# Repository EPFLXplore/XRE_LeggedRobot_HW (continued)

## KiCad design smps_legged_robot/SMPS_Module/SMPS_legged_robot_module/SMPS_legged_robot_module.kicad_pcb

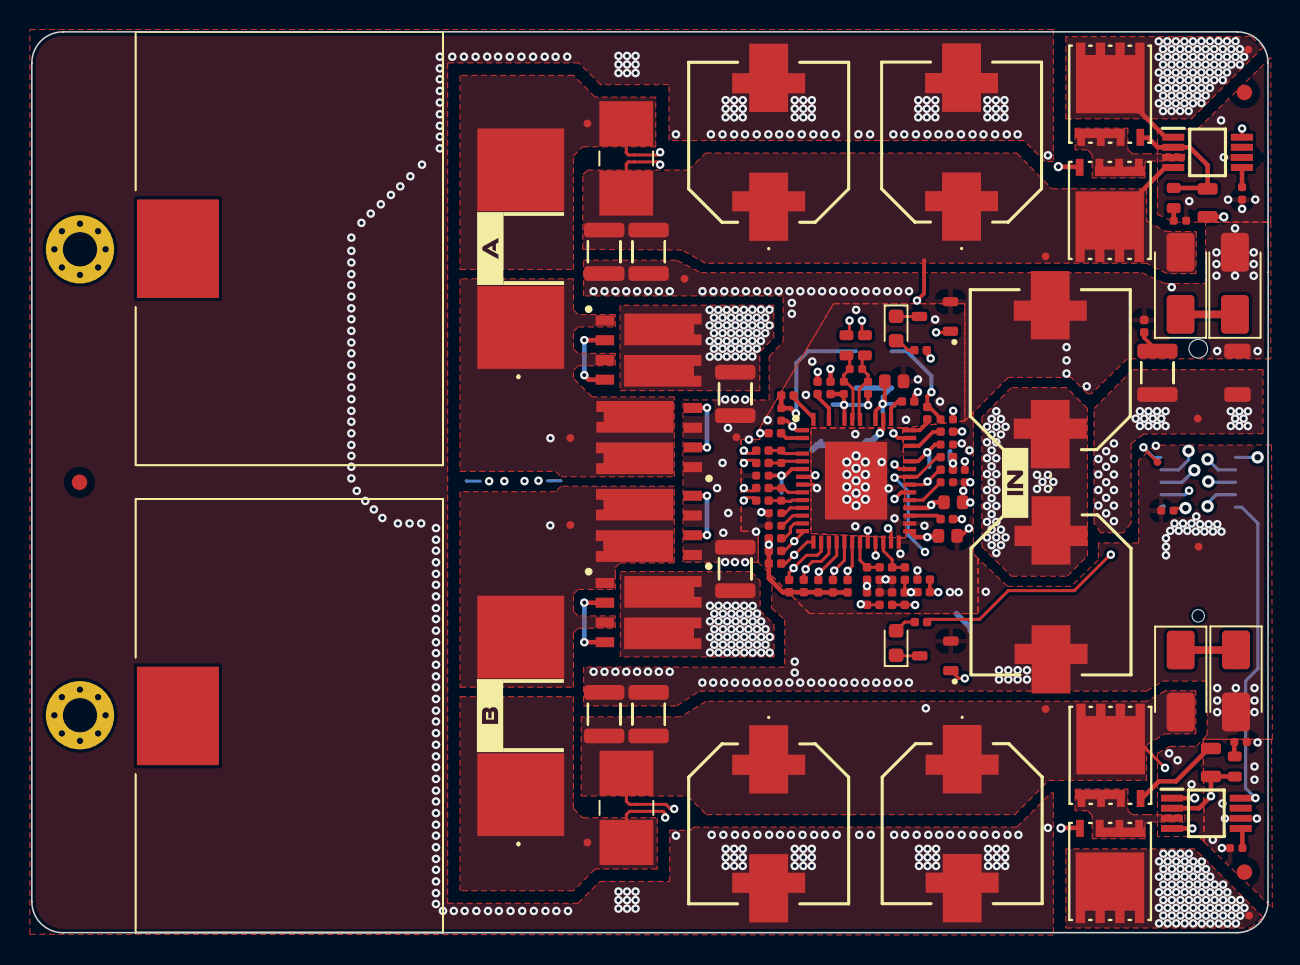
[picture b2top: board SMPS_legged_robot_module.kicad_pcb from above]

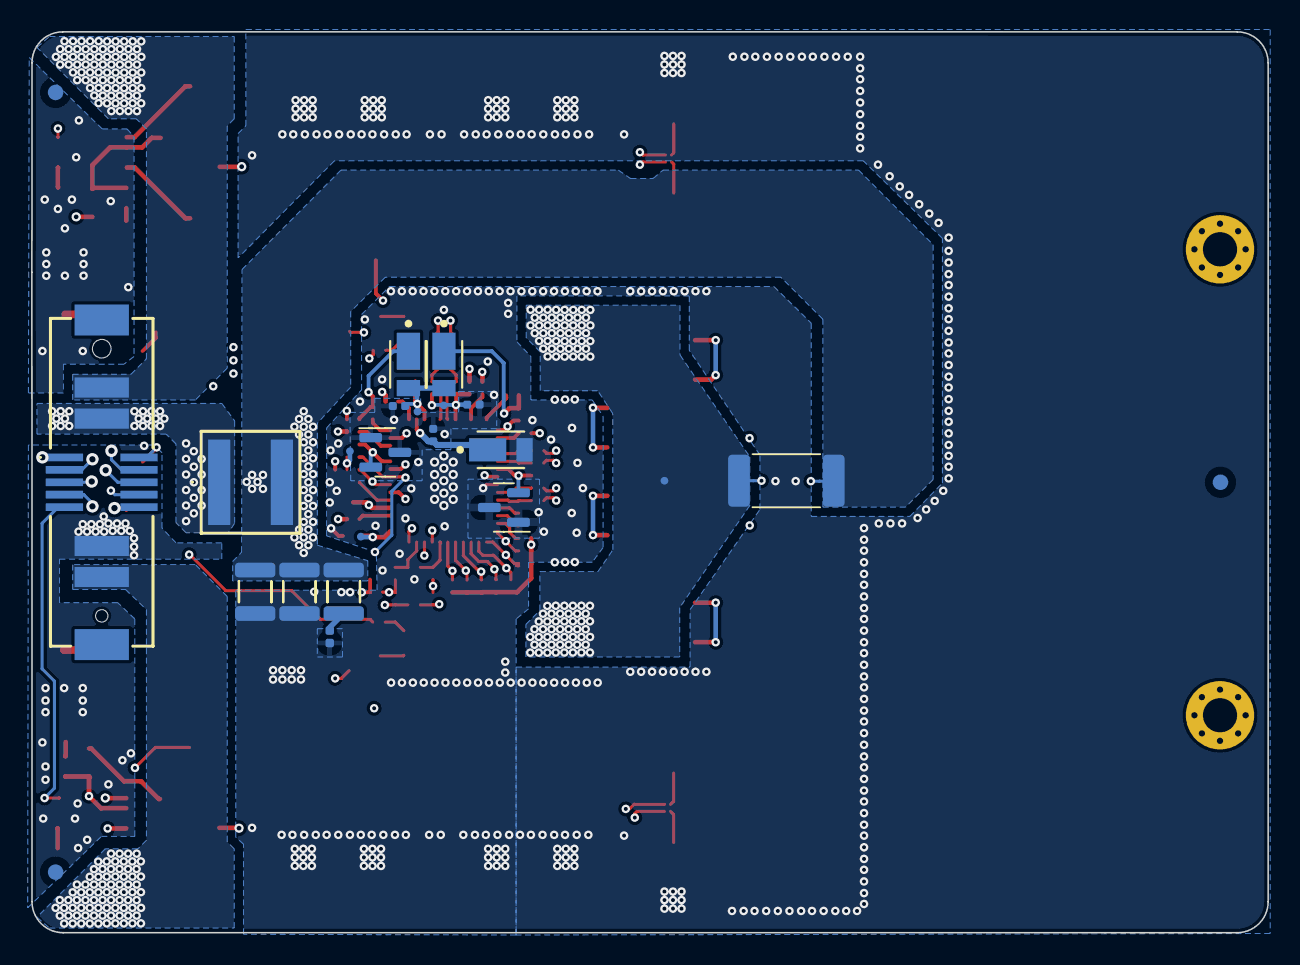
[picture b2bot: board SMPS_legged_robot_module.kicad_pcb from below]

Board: 6 copper layers, 79.6 x 58.0 mm, 156 parts (25 on the bottom side), 83 nets.

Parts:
C401, C601, C603, C702, C715: 100n X7R 50V; C_0402_1005_DensityHigh
C602, C604, C708, C713, C718, C722, C723: 10n X7R 100V; C_0402_1005_DensityHigh
C607: 1u X7R 25V; C_0603_1608_DensityHigh
C701, C706, C707, C714, C731, C732, C901, C903, C906, C907: 10uF X7R 100V; C_1210_3225_DensityHigh
C703, C720, C725: 1n X7R 100V; C_0402_1005_DensityHigh
C704, C705, C729, C730: 120u CAN 50V; Hybrid_G_VP
C709, C712: 33p X7R 25V; C_0402_1005_DensityHigh
C710, C711: 6.8n X7R 25V; C_0402_1005_DensityHigh
C716, C726: 2.2u X7R 25V; C_0603_1608_DensityHigh
C717, C724: 4.7u X5R 25V; C_0402_1005_DensityHigh
C902: 4u7 X7R 100V; C_1206_3216_DensityHigh
C904, C905: 56u CAN 63V; Hybrid_G_VP
D601, D602, D703: DFLS1100-7; Diodes_Inc.-PowerDI123-03_2017-0-MFG
D603, D605: SMAJ28A; D_SMA
D604, D606: SMAJ33A; D_SMA
D701, D702: GREEN; LED_0603_1608Metric
FM701, FM702, FM703, FM704, FM705, FM706: Fiducial; Fiducial_1mm_Mask2mm
H801, H802: M2 (2.2mm); MountingHole_2.2mm_M2_Pad_Via
IC601, IC602: LTC4372CMS8#TRPBF; SOP65P490X110-8N
IC701: LTC3889EUKG#PBF; QFN50P700X800X80-53N-D
J401: 10159559-410221RLF; 10159559410221RLF
L701, L702: 4,7uH; PQ2617BHA4R7K
L901: 1u XEL6060-102MEB; XEL6060102MEC
NT601, NT602, NT603, NT604, NT605, NT606: NetTie_2; NetTie-2_SMD_Pad0.2mm
Q601, Q602, Q603, Q604: BSC016N06NSATMA1; PG-TDSON-8_INF
Q701, Q702, Q705, Q706: IPG20N06S4L26AATMA1; Infineon-IPG20N06S4L-26A-Manufacturer_Recommended
Q703, Q704: PMBT3906,215; SOT-23
Q707, Q708: NX3020NAK,215; SOT-23-3
R601, R603: 10R 1% 1/8W; R_0805_2012_DensityHigh
R602, R604, R727, R728: 1k 1% 1/10W; R_0603_1608_DensityHigh
R701: 5k 1% 1/16W; R_0402_1005_DensityHigh
R702, R703, R704, R705, R706, R707, R708, R709, R710, R711: 10k 1% 1/16W; R_0402_1005_DensityHigh
R712, R713, R714, R715, R716, R718, R719, R720, R721, R722: R; R_0402_1005_DensityHigh
R717, R729: 3m 1% 3W; RESC6432X135N
R723, R724, R730, R731, R901, R902: 10R 1% 1/8W; R_0402_1005_DensityHigh
R725: 2m 1% 3W; R_2512_6332Metric_Pad1.40x3.35mm_HandSolder
R726, R732, R733, R734, R735, R738, R739: 2R 1% 1/8W; R_0402_1005_DensityHigh
R736, R737: 470R 1% 1/8W; R_0402_1005_DensityHigh
TP401: FAULT0; TestPoint_Pad_D0.5mm_Front
TP402: FAULT1; TestPoint_Pad_D0.5mm_Front
TP403: SDA; TestPoint_Pad_D0.5mm_Front
TP404: SCL; TestPoint_Pad_D0.5mm_Front
TP405: RUN0; TestPoint_Pad_D0.5mm_Front
TP406: RUN1; TestPoint_Pad_D0.5mm_Front
TP407: ALERT; TestPoint_Pad_D0.5mm_Front
TP408: +VBAT_IN; TestPoint_Pad_D0.5mm_Front
TP409: +12V; TestPoint_Pad_D0.5mm_Front
TP410, TP413, TP414: GND; TestPoint_Pad_D0.5mm_Front
TP411: MVA; TestPoint_Pad_D0.5mm_Front
TP412: MVB; TestPoint_Pad_D0.5mm_Front
TP701: VIN; TestPoint_Pad_D0.5mm_Front
TP702: SW0; TestPoint_Pad_D0.5mm_Front
TP703: SW1; TestPoint_Pad_D0.5mm_Front
TP704: 2V5LTC; TestPoint_Pad_D0.5mm_Back
TP705: 3V3LTC; TestPoint_Pad_D0.5mm_Back
TP706: DRVCC; TestPoint_Pad_D0.5mm_Back
TP707: MVB_OUT; TestPoint_Pad_D0.5mm_Front
TP708: MVA_OUT; TestPoint_Pad_D0.5mm_Front
TP709: VIN_MOS; TestPoint_Pad_D0.5mm_Front
TP710: SW0_L; TestPoint_Pad_D0.5mm_Front
TP711: SW1_L; TestPoint_Pad_D0.5mm_Front
kibuzzard-66485E02: G***; kibuzzard-66485E02
kibuzzard-66485E57: G***; kibuzzard-66485E57
kibuzzard-66485E80: G***; kibuzzard-66485E80

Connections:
+2V5LTC: C726.2, IC701.27 (VDD25), R712.1, R713.1, R714.1, R715.1, R716.1, TP704.1
+3.3VLTC: C716.2, IC701.30 (VDD33), R701.2, R702.2, R703.2, R704.2, R705.2, R706.2, R707.2, R708.2, R709.2, R710.2, R711.2, TP705.1
+12V: C401.1, C717.2, D703.1 (K), IC701.43 (EXTVCC), J401.S10, R736.1, R737.1, TP409.1
/Project Architecture/+VBAT_Filtered: C903.1, C904.1, C905.1, C906.1, C907.1, L901.2, NT602.1, R725.1, R726.2
/Project Architecture/+VBAT_IN: C901.1, C902.1, J401.P1, L901.1, TP408.1
/Project Architecture/MVA_FILTERED: IC601.1 (OUT), J401.P3, Q602.1 (D), TP411.1
/Project Architecture/MVB_FILTERED: IC602.1 (OUT), J401.P4, Q604.1 (D), TP412.1
/Project Architecture/Power - Connector /MVA_SHDN: IC601.8 (SHDN), J401.S8
/Project Architecture/Power - Connector /MVB_SHDN: IC602.8 (SHDN), J401.S9
/Project Architecture/Power - Connector /RUN0: IC701.19 (RUN0), J401.S4, R705.1, TP405.1
/Project Architecture/Power - Connector /RUN1: IC701.20 (RUN1), J401.S2, R704.1, TP406.1
/Project Architecture/Power - Connector /SCL: IC701.14 (SCL), J401.S1, R710.1, TP404.1
/Project Architecture/Power - Connector /SDA: IC701.15 (SDA), J401.S3, R711.1, TP403.1
/Project Architecture/Power - Connector /~ALERT: IC701.16 (~ALERT), J401.S5, R709.1, TP407.1
/Project Architecture/Power - Connector /~FAULT0: IC701.17 (~FAULT0), J401.S7, R708.1, TP401.1
/Project Architecture/Power - Connector /~FAULT1: IC701.18 (~FAULT1), J401.S6, R707.1, TP402.1
/Project Architecture/Power - Converter/DRVCC: C607.2, C724.2, D601.2 (A), D602.2 (A), IC701.44 (DRVCC), TP706.1
/Project Architecture/Power - Converter/MVA_OUT: C704.1, C705.1, C706.1, C707.1, D603.2 (A2), IC601.4 (IN), IC701.7 (VSENSE0+), NT606.1, Q601.1 (D), R717.2, TP708.1
/Project Architecture/Power - Converter/MVB_OUT: C729.1, C730.1, C731.1, C732.1, D605.2 (A2), IC602.4 (IN), IC701.35 (VSENSE1+), NT604.1, Q603.1 (D), R729.2, TP707.1
/Project Architecture/Power - Converter/PGOOD0: IC701.34 (PGOOD0), Q707.1 (G), R702.1
/Project Architecture/Power - Converter/PGOOD1: IC701.33 (PGOOD1), Q708.1 (G), R703.1
/Project Architecture/Power - Converter/SHARE_CLK: IC701.29 (SHARE_CLK), R706.1
/Project Architecture/Power - Converter/SW0: C702.2, IC701.1 (SW0), L701.1, Q701.3 (S), Q702.1 (D), TP702.1
/Project Architecture/Power - Converter/SW0_L: L701.2, NT605.1, R717.1, TP710.1
/Project Architecture/Power - Converter/SW1: C715.2, IC701.39 (SW1), L702.2, Q705.3 (S), Q706.1 (D), TP703.1
/Project Architecture/Power - Converter/SW1_L: L702.1, NT603.1, R729.1, TP711.1
/Project Architecture/Power - Converter/SYNC: IC701.13 (SYNC), R701.1
/Project Architecture/Power - Converter/VIN: C718.2, C722.2, C723.2, IC701.48 (VIN), R726.1, TP701.1
/Project Architecture/Power - Converter/VIN_MOS: C701.1, C714.1, NT601.1, Q701.1 (D), Q705.1 (D), R725.2, TP709.1
/Project Architecture/Power - Converter/shuntA+: NT606.2, R724.2
/Project Architecture/Power - Converter/shuntA-: NT605.2, R723.2
/Project Architecture/Power - Converter/shuntB+: NT604.2, R731.2
/Project Architecture/Power - Converter/shuntB-: NT603.2, R730.2
/Project Architecture/Power - Converter/shuntIn+: NT601.2, R728.1
/Project Architecture/Power - Converter/shuntIn-: NT602.2, R727.1
GND: C401.2, C601.2, C602.1, C603.2, C604.1, C607.1, C701.2, C704.2, C705.2, C706.2, C707.2, C708.1, C709.1, C710.1, C711.1, C712.1, C713.1, C714.2, C716.1, C717.1, C718.1, C724.1, C726.1, C729.2, C730.2, C731.2, C732.2, C902.2, C904.2, C905.2, C906.2, C907.2, D604.2 (A2), D606.2 (A2), D703.2 (A), IC601.6 (GND), IC602.6 (GND), IC701.8 (VSENSE0-), IC701.26 (PHAS_CFG), IC701.28 (WP), IC701.53 (GND), J401.P2, Q702.3 (S), Q703.1 (B), Q703.3 (C), Q704.1 (B), Q704.3 (C), Q706.3 (S), Q707.2 (S), Q708.2 (S), R718.2, R719.2, R720.2, R721.2, R722.2, R901.1, R902.1, TP410.1, TP413.1, TP414.1
unnamed: C602.2, R602.2
unnamed: C604.2, R604.2
unnamed: C901.2, R901.2
unnamed: C903.2, R902.2
unnamed: C715.1, D601.1 (K), R738.1
unnamed: C702.1, D602.1 (K), R739.1
unnamed: D603.1 (A1), D604.1 (A1)
unnamed: D605.1 (A1), D606.1 (A1)
unnamed: D701.2 (A), R736.2
unnamed: D701.1 (K), Q707.3 (D)
unnamed: D702.2 (A), R737.2
unnamed: D702.1 (K), Q708.3 (D)
unnamed: IC601.2 (GATE), Q602.2 (G), R601.2, R602.1
unnamed: C601.1, IC601.5 (INTVCC)
unnamed: IC601.3 (SOURCE), Q601.3 (S), Q602.3 (S)
unnamed: IC602.2 (GATE), Q604.2 (G), R603.2, R604.1
unnamed: C603.1, IC602.5 (INTVCC)
unnamed: IC602.3 (SOURCE), Q603.3 (S), Q604.3 (S)
unnamed: C720.1, C722.1, IC701.47 (IIN+), R727.2
unnamed: C720.2, C723.1, IC701.46 (IIN-), R728.2
unnamed: IC701.21 (ASEL0), R714.2, R720.1
unnamed: IC701.22 (ASEL1), R715.2, R721.1
unnamed: IC701.25 (FREQ_CFG), R716.2, R722.1
unnamed: C709.2, IC701.12 (ITH0)
unnamed: C712.2, IC701.31 (ITH1)
unnamed: C710.2, IC701.11 (ITHR0)
unnamed: C711.2, IC701.32 (ITHR1)
unnamed: C708.2, IC701.6 (TSNS0), Q703.2 (E)
unnamed: C713.2, IC701.36 (TSNS1), Q704.2 (E)
unnamed: IC701.23 (VOUT0_CFG), R712.2, R718.1
unnamed: IC701.24 (VOUT1_CFG), R713.2, R719.1
unnamed: IC701.50 (BG0), R732.2
unnamed: IC701.52 (BOOST0), R739.2
unnamed: C703.1, IC701.4 (ISENSE0+), R723.1
unnamed: C703.2, IC701.5 (ISENSE0-), R724.1
unnamed: IC701.2 (TG0), R733.2
unnamed: IC701.42 (BG1), R734.2
unnamed: IC701.40 (BOOST1), R738.2
unnamed: C725.1, IC701.9 (ISENSE1+), R730.1
unnamed: C725.2, IC701.10 (ISENSE1-), R731.1
unnamed: IC701.38 (TG1), R735.2
unnamed: Q601.2 (G), R601.1
unnamed: Q603.2 (G), R603.1
unnamed: Q701.2 (G), R733.1
unnamed: Q702.2 (G), R732.1
unnamed: Q705.2 (G), R735.1
unnamed: Q706.2 (G), R734.1

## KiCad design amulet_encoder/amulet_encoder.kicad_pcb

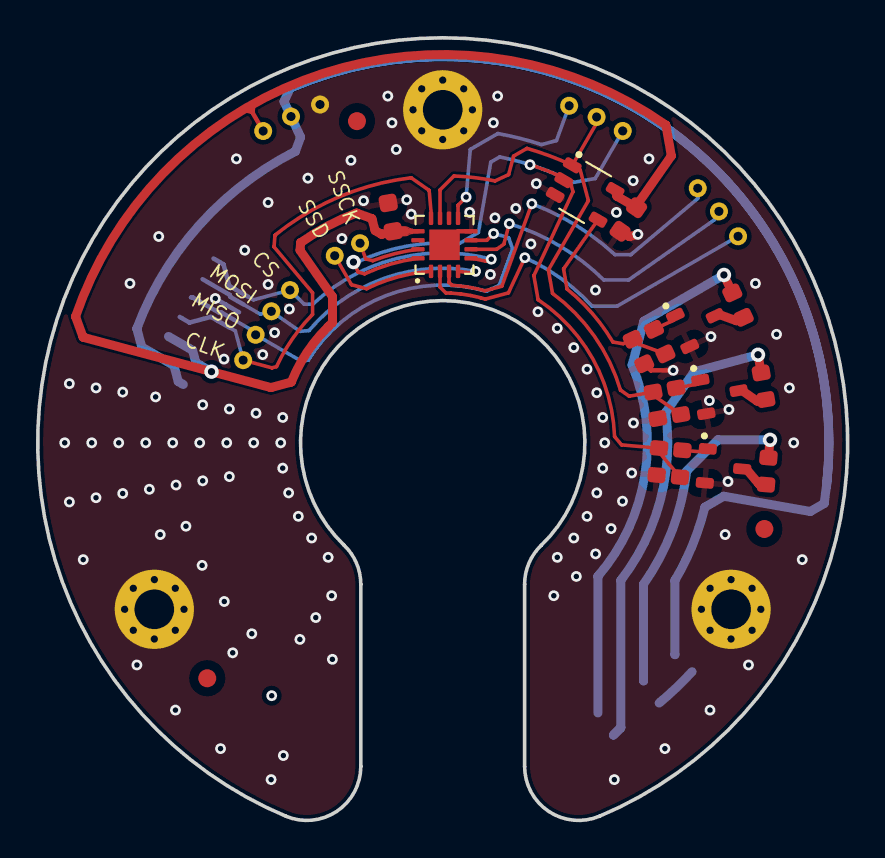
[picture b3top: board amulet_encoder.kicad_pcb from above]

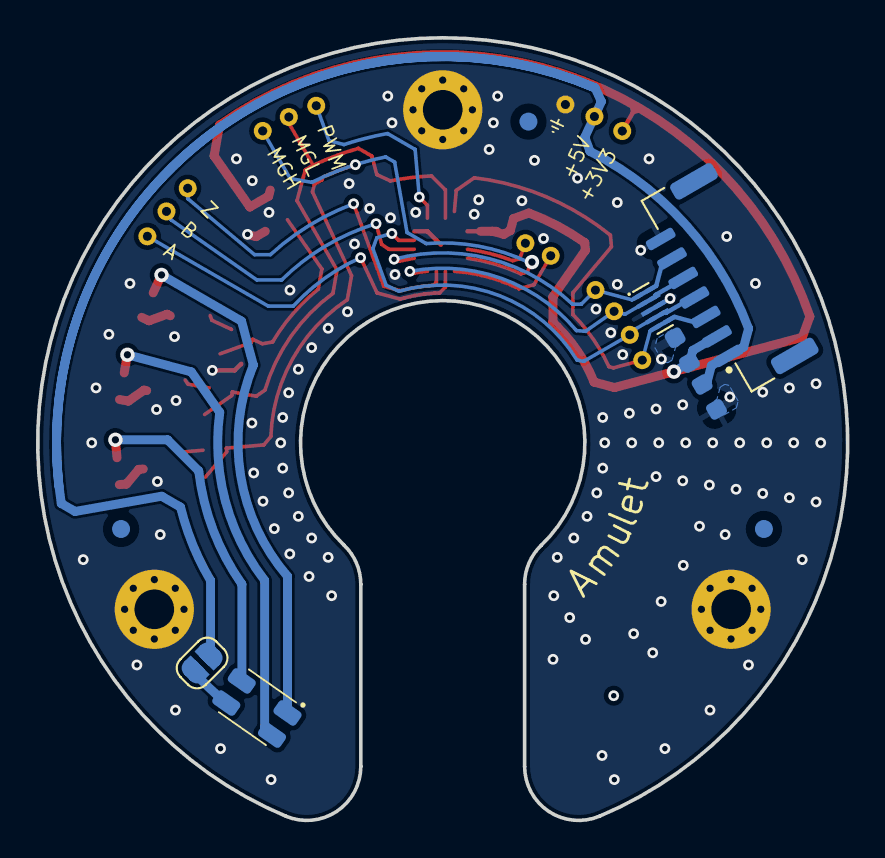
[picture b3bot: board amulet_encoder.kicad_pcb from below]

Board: 4 copper layers, 45.0 x 43.5 mm, 46 parts (12 on the bottom side), 26 nets.

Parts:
C1, C2: 100n X7R 100V; C_0603_1608_DensityMedium
C3, C4: 1u X7R 25V; C_0603_1608_DensityMedium
D1: PESD4USB5B-TBSX; SOT1176D
D2: SMTL4-SRGY; 4-PLCC
FM1, FM2, FM3, FM4, FM5, FM6: Fiducial; Fiducial_1mm_Mask2mm
H1, H3: M2; MountingHole_2.2mm_M2_Pad_Via
H2: e; MountingHole_2.2mm_M2_Pad_Via
J1: SM07B-GHS-TB; JST_GH_SM07B-GHS-TB_1x07-1MP_P1.25mm_Horizontal
JP1: PWR_LED; SolderJumper-2_P1.3mm_Open_RoundedPad1.0x1.5mm
Q1, Q2, Q3: PMV90ENER; SOT-23-3
R1, R3, R4: 1k 1/10W 1%; R_0603_1608_DensityMedium
R2, R5, R6: 100k 1/10W 1%; R_0603_1608_DensityMedium
R7: 200R 1/5W 1%; R_0603_1608_DensityMedium
R8, R9: 330R 1/5W 1%; R_0603_1608_DensityMedium
TP1: CLK; TestPoint_Pad_D1mm_THT
TP2: MISO; TestPoint_Pad_D1mm_THT
TP3: MOSI; TestPoint_Pad_D1mm_THT
TP4: CS; TestPoint_Pad_D1mm_THT
TP5: SSD; TestPoint_Pad_D1mm_THT
TP6: SSCK; TestPoint_Pad_D1mm_THT
TP7: A; TestPoint_Pad_D1mm_THT
TP8: B; TestPoint_Pad_D1mm_THT
TP9: Z; TestPoint_Pad_D1mm_THT
TP10: PWM; TestPoint_Pad_D1mm_THT
TP11: MGH; TestPoint_Pad_D1mm_THT
TP12: MGL; TestPoint_Pad_D1mm_THT
TP13: +3V3; TestPoint_Pad_D1mm_THT
TP14: +5V; TestPoint_Pad_D1mm_THT
TP15: GND; TestPoint_Pad_D1mm_THT
U1: MA732GQ; QFN-16
U2: SN74AHC1G02DBVR; SOT95P280X145-5N

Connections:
+3V3: C2.1, C3.1, C4.1, J1.2, TP13.1, U1.13 (VDD), U2.5 (VCC)
+5V: C1.1, J1.1, JP1.2 (B), TP14.1
/A: TP7.1, U1.2 (A)
/B: TP8.1, U1.6 (B)
/CLK: D1.5 (K), D1.6 (K), J1.3, TP1.1, U1.12 (SCLK)
/CS: D1.1 (K), D1.10 (K), J1.6, TP4.1, U1.5 (CS)
/LED_A: D2.4 (A), JP1.1 (A)
/LED_G_K: D2.1 (K1), R7.1
/LED_R_K: D2.3 (K3), R9.1
/LED_Y_K: D2.2 (K2), R8.1
/MG: R1.2, R2.1, U2.4
/MGH: R3.2, R5.1, TP11.1, U1.16 (MGH), U2.2
/MGL: R4.2, R6.1, TP12.1, U1.11 (MGL), U2.1
/MISO: D1.4 (K), D1.7 (K), J1.4, TP2.1, U1.7 (MISO)
/MOSI: D1.2 (K), D1.9 (K), J1.5, TP3.1, U1.4 (MOSI)
/MOS_G_D: Q1.3 (D), R7.2
/MOS_G_G: Q1.1 (G), R1.1
/MOS_R_D: Q3.3 (D), R9.2
/MOS_R_G: Q3.1 (G), R4.1
/MOS_Y_D: Q2.3 (D), R8.2
/MOS_Y_G: Q2.1 (G), R3.1
/PWM: TP10.1, U1.9 (PWM)
/SSCK: TP6.1, U1.15 (SSCK)
/SSD: TP5.1, U1.1 (SSD)
/Z: TP9.1, U1.3 (Z)
GND: C1.2, C2.2, C3.2, C4.2, D1.3 (A), D1.8 (A), H1.1, H2.1, H3.1, J1.7, Q1.2 (S), Q2.2 (S), Q3.2 (S), R2.2, R5.2, R6.2, TP15.1, U1.8 (GND), U1.10 (TEST), U1.17 (PAD), U2.3 (GND)

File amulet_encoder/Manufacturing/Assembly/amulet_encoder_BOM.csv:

"Item","Qty","Reference(s)","Value","Datasheet","DNP","Footprint","Description","Manufacturer","Manufacturer ","Manufacturer Part Number","Package","Supplier 1","Supplier Part Number 1"
"1","2","C1-2","100n X7R 100V","https://mm.digikey.com/Volume0/opasdata/d220001/medias/docus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","","0_capacitor_smd:C_0603_1608_DensityMedium","0.1 µF ±10% 100V Ceramic Capacitor X7R 0603 (1608 Metric)","Taiyo Yuden","","HMK107B7104KAHT","0603","Digikey","587-6009-1-ND"
"2","2","C3-4","1u X7R 25V","https://mm.digikey.com/Volume0/opasdata/d220001/medias/docus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","","0_capacitor_smd:C_0603_1608_DensityMedium","1 µF ±10% 25V Ceramic Capacitor X7R 0603 (1608 Metric)","Taiyo Yuden","","TMK107AB7105KAHT","0603","Digikey","587-3467-1-ND"
"3","1","D1","PESD4USB5B-TBSX","https://assets.nexperia.com/documents/data-sheet/PESD4USB5B-TBS.pdf","","0_package_DFN_QFN:SOT1176D","5.5V (Typ) Clamp 7A (8/20µs) Ipp Tvs Diode Surface Mount, Wettable Flank DFN2510D-10","Nexperia USA Inc.","","PESD4USB5B-TBSX","","Digikey","1727-PESD4USB5B-TBSXCT-ND"
"4","1","D2","SMTL4-SRGY","https://www.bivar.com/parts_content/Datasheets/SMTL4-SRGY.pdf","","0_led:4-PLCC","Green, Red, Yellow 525nm Green, 625nm Red, 591nm Yellow LED Indication - Discrete 3.3V Green, 1.9V Red, 1.9V Yellow 4-PLCC","Bivar Inc.","","SMTL4-SRGY","","Digikey","492-2193-1-ND"
"5","1","J1","SM07B-GHS-TB","https://www.jst-mfg.com/product/pdf/eng/eGH.pdf","","0_connectors:JST_GH_SM07B-GHS-TB_1x07-1MP_P1.25mm_Horizontal","Connector Header Surface Mount, Right Angle 7 position 0.049"" (1.25mm)","JST Sales America Inc.","","SM07B-GHS-TB","","Digikey","455-1569-1-ND"
"6","3","Q1-3","PMV90ENER","https://assets.nexperia.com/documents/data-sheet/PMV90ENE.pdf","","0_package_SOT_TO_SMD:SOT-23-3","N-Channel 30 V 3A (Ta) 460mW (Ta) Surface Mount TO-236AB","Nexperia USA Inc.","","PMV90ENER","","Digikey","1727-2735-1-ND"
"7","3","R1, 3-4","1k 1/10W 1%","https://www.yageo.com/upload/media/product/products/datashee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","","0_resistor_smd:R_0603_1608_DensityMedium","1 kOhms ±1% 0.1W, 1/10W Chip Resistor 0603 (1608 Metric) Moisture Resistant Thick Film","YAGEO","","RC0603FR-071KL","0603","Digikey","311-1.00KHRCT-ND"
"8","3","R2, 5-6","100k 1/10W 1%","https://www.yageo.com/upload/media/product/products/datashee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","","0_resistor_smd:R_0603_1608_DensityMedium","100 kOhms ±1% 0.1W, 1/10W Chip Resistor 0603 (1608 Metric) Moisture Resistant Thick Film","YAGEO","","RC0603FR-07100KL","0603","Digikey","311-100KHRCT-ND"
"9","1","R7","200R 1/5W 1%","https://www.yageo.com/upload/media/product/productsearch/dat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","","0_resistor_smd:R_0603_1608_DensityMedium","200 Ohms ±1% 0.2W, 1/5W Chip Resistor 0603 (1608 Metric) Automotive AEC-Q200, Moisture Resistant Thick Film","YAGEO","","AC0603FR-7W200RL","0603","Digikey","13-AC0603FR-7W200RLCT-ND"
"10","2","R8-9","330R 1/5W 1%","https://www.te.com/usa-en/product-2176177-5.datasheet.pdf","","0_resistor_smd:R_0603_1608_DensityMedium","330 Ohms ±1% 0.2W, 1/5W Chip Resistor 0603 (1608 Metric) Thick Film","TE Connectivity Passive Product","","CRGH0603F330R","0603","Digikey","A129541CT-ND"
"11","1","U1","MA732GQ","https://www.monolithicpower.com/en/documentview/productdocum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","","0_package_DFN_QFN:QFN-16","14-Bit, Digital, Contactless Angle Sensor with ABZ Incremental & PWM Outputs","Monolithic Power Systems Inc.","","MA732GQ-Z","","Digikey","1589-MA732GQ-ZCT-ND"
"12","1","U2","SN74AHC1G02DBVR","https://www.ti.com/lit/ds/symlink/sn74ahc1g02.pdf","","0_package_SOT_TO_SMD:SOT95P280X145-5N","SN74AHC1G02 Single 2-Input Positive-NOR Gate","Texas Instruments","Texas Instruments","SN74AHC1G02DBVR","","Digikey","296-1088-1-ND"
